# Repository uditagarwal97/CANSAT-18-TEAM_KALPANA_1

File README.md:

View this project on [CADLAB.io](https://cadlab.io/project/1174). 

# CANSAT-18-TEAM_KALPANA_1
This Repository contains all the code developed during CANSAT'18 compitition by Team Kalpana-1(ID 2426).

## About the CanSat compition
This annual competition is open to teams from universities and colleges. Teams were asked to design and build a space-type system, following the approved competition guide, and then compete against each at the end of two semesters to determine the winners. For more information please head over to: 
[Compitition website](http://www.cansatcompetition.com/index.html)

## Our problem statement
The 2018 mission simulates a space probe (CanSat) entering a planetary atmosphere. The probe shall carry a single large hen's egg. The egg must survive all portions of flight. The operation sequence shall be:

1. The probe is launched to an altitude of 670 meters to 725 meters and then deployed from the rocket. Orientation of deployment is not controlled and is most definitely violent.

2. Once deployed, the probe shall open an aero-braking heat shield. The descent rate shall be kept at 10 to 30 meters/sec. The aero-braking probe must maintain a stable orientation with the heat shield facing the direction of descent during descent. Tumbling is not allowed. Active control surfaces or other non pyrotechnic mechanisms can be used to maintain orientation.

3. At an altitude of 300 meters, the probe shall release the aero-braking heat shield and simultaneously deploy a parachute to reduce the descent rate of 5 meters/sec.

4. The probe shall land leaving the egg intact.

The probe shall include sensors for tracking altitude using air pressure, external temperature, battery voltage and GPS position. A compartment shall be included to hold a large hen's egg. The egg will simulate a delicate instrument. 

Visit the following link for detailed info of our approach: [Link](http://uditagarwal.in/wiki/index.php/CANSAT18)

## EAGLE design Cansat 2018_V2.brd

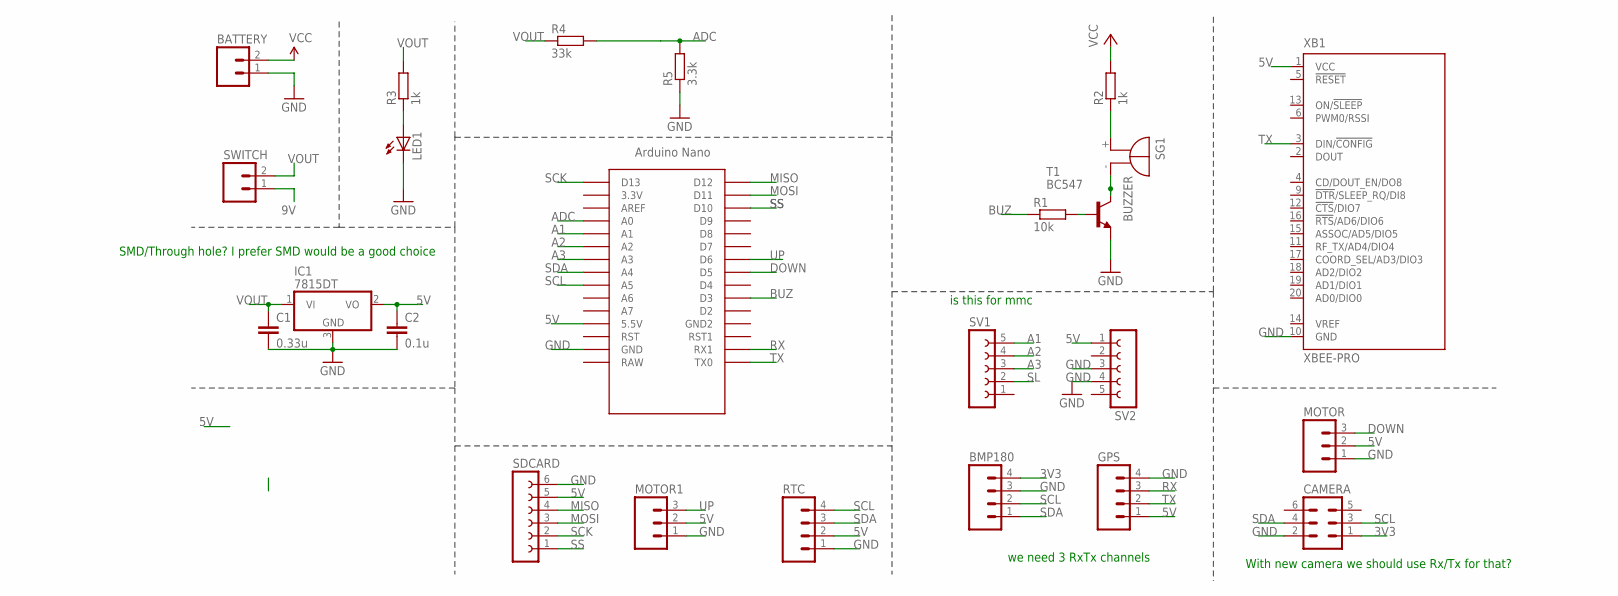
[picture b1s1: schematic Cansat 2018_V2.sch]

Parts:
BATTERY: M02; 02P
BMP180: M04; 04P
C1: 0.33u; C0805
C2: 0.1u; C0805
CAMERA: MA03-2
GPS: M04; 04P
IC1: 7815DT; TO252
LED1: LED3MM
MOTOR, MOTOR1: M03; 03P
R1: 10k; 0207/7
R2: 1k; 0207/7
R3: 1k; 0204/7
R4: 33k; 0207/7
R5: 3.3k; 0207/10
RTC: M04; 04P
SDCARD: FE06-1; FE06
SG1: BUZZER; F/TMB
SV1, SV2: FE05-1
SWITCH: M02; 02P
T1: BC547; TO92
U$1: NANO
XB1: XBEE-PRO

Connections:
3V3: BMP180.4, CAMERA.1, R2.2
5V: C2.1, GPS.1, IC1.2 (VO), MOTOR.2, MOTOR1.2, RTC.2, SDCARD.5, SV2.1, U$1.5V (5.5V), XB1.1 (VCC)
9V: BATTERY.2, SWITCH.1
A1: SV1.5, U$1.A1
A2: SV1.4, U$1.A2
A3: SV1.3, U$1.A3
ADC: R5.2, U$1.A0
BUZ: R1.1, U$1.D3
DOWN: MOTOR.3, U$1.D5
GND: BATTERY.1, BMP180.3, C1.2, C2.2, CAMERA.2, GPS.4, IC1.3 (GND), LED1.K (C), MOTOR.1, MOTOR1.1, R5.1, RTC.1, SDCARD.6, SV2.3, SV2.4, T1.1 (E), U$1.GND, XB1.10 (GND)
MISO: SDCARD.4, U$1.D12
MOSI: SDCARD.3, U$1.D11
unnamed: R1.2, T1.2 (B)
unnamed: SG1.-, T1.3 (C)
unnamed: R2.1, SG1.+
unnamed: LED1.A, R3.1
RX: GPS.3, U$1.RX1
SCK: SDCARD.2, U$1.D13
SCL: BMP180.2, CAMERA.3, RTC.4, U$1.A5
SDA: BMP180.1, CAMERA.4, RTC.3, U$1.A4
SL: SV1.2
SS: SDCARD.1, U$1.D10
TX: GPS.2, U$1.TX0, XB1.3 (DIN/!CONFIG)
UP: MOTOR1.3, U$1.D6
VOUT: C1.1, IC1.1 (VI), R3.2, R4.1, SWITCH.2

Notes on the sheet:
SMD/Through hole? I prefer SMD would be a good choice
With new camera we should use Rx/Tx for that?
we need 3 RxTx channels
is this for mmc

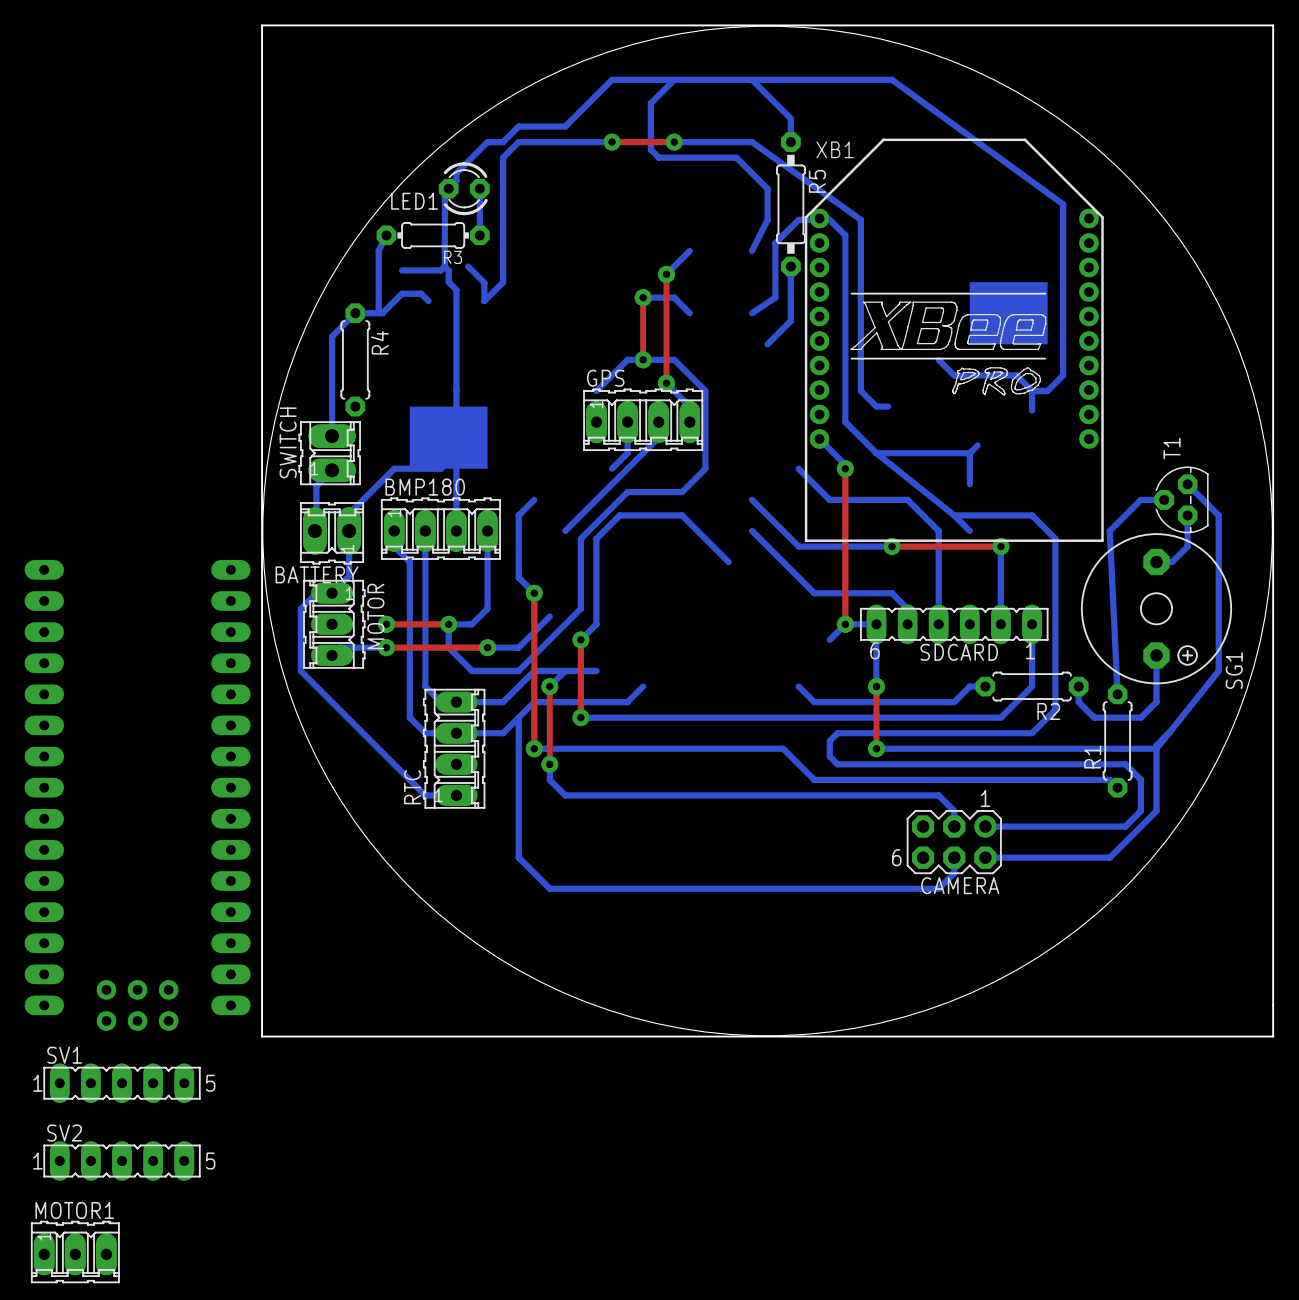
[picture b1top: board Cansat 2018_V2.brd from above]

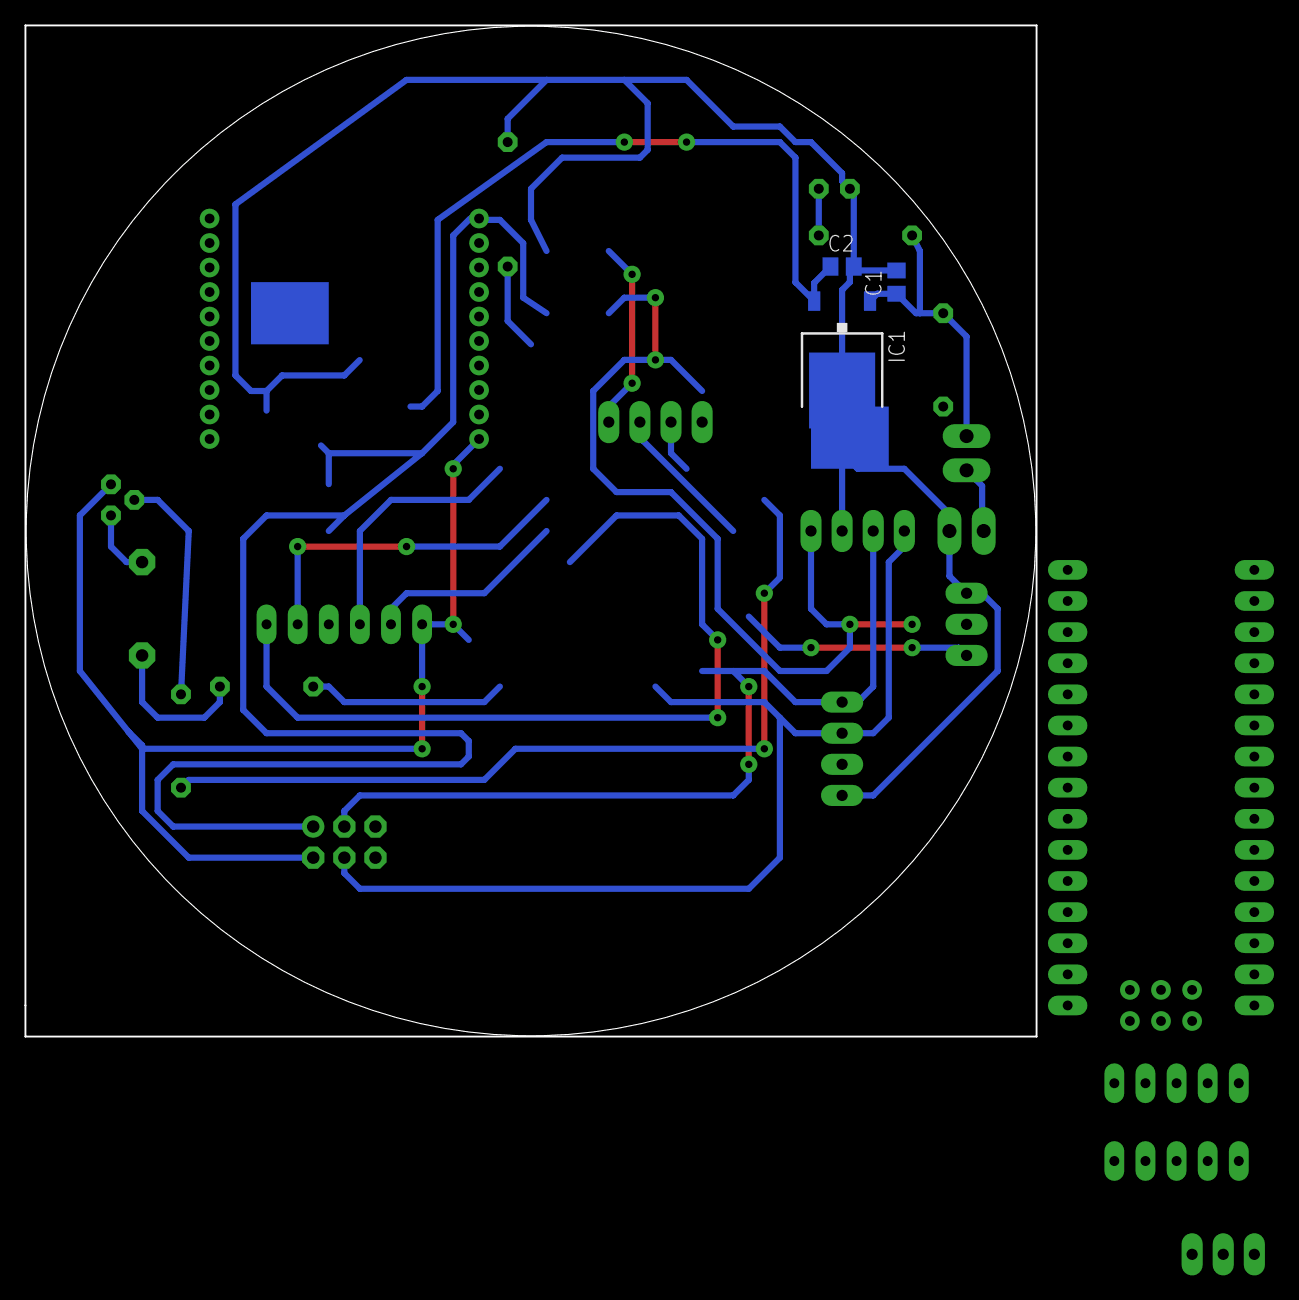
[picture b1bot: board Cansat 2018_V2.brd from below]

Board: 2 copper layers, 82.5 x 82.5 mm, 24 parts (3 on the bottom side), 24 nets.

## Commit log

2018-05-28 Updated View
2018-05-28 Added event handlers
2018-05-28 Updated event handlers
2018-05-28 Added eagle CAD design files
2018-06-15 Backlink to CADLAB.io has been added.
2018-06-15 Updated latest design files
2018-06-15 Resolved merge conflicts
2019-10-01 Update README.md
    Added information regarding the competition and problem statement

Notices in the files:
parts and their libraries:
SparkFun-Aesthetics: Licensing: Creative Commons ShareAlike 4.0 International - https://creativecommons.org/licenses/by-sa/4.0
